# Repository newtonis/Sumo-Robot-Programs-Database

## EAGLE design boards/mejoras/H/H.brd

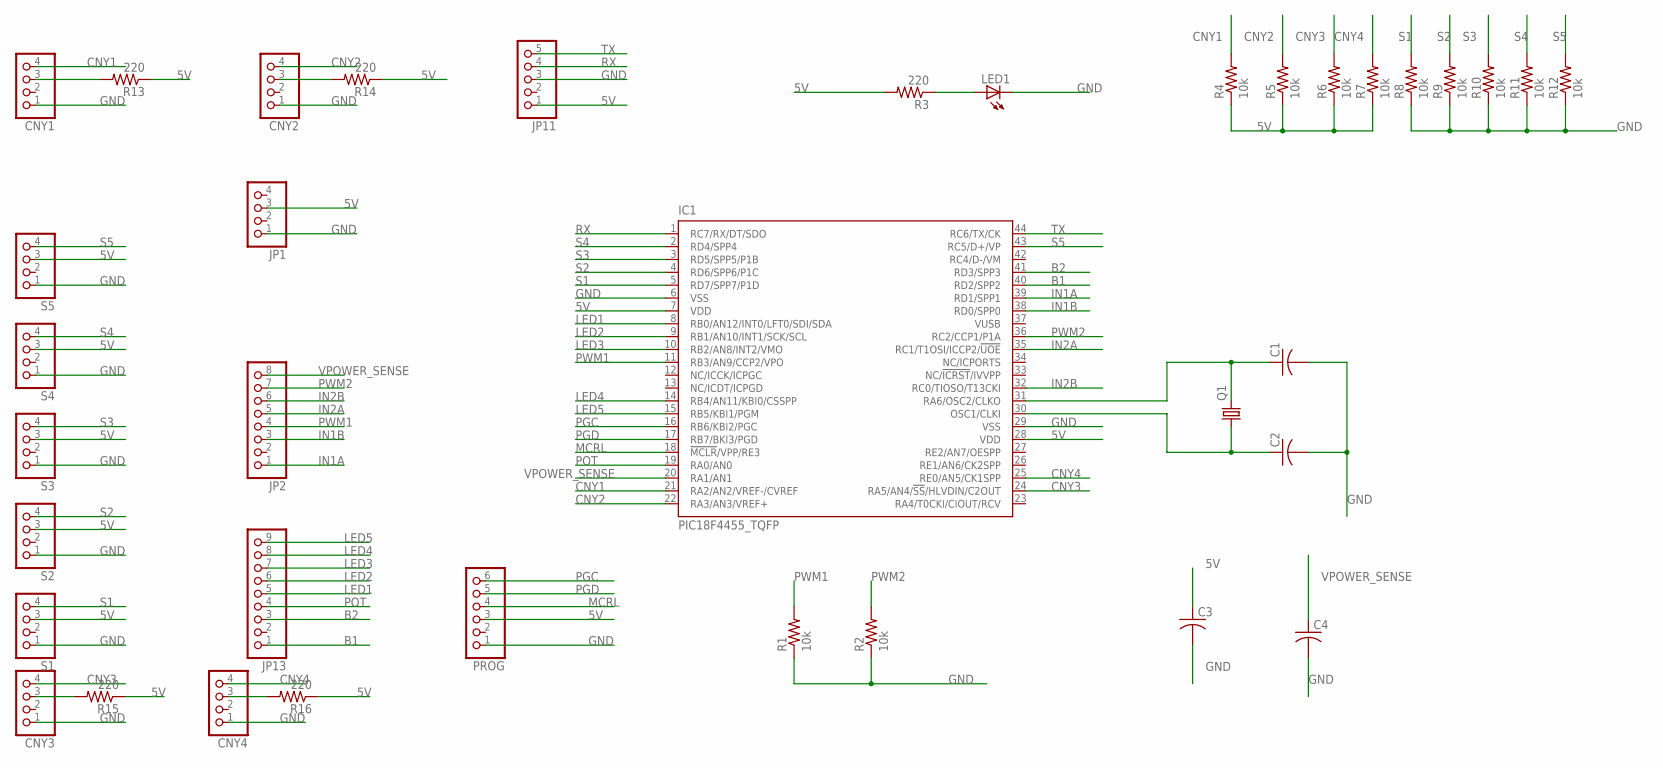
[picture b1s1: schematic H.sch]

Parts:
C1, C2, C3, C4: C-USC0805K; C0805K
CNY1, CNY2, CNY3, CNY4: PINHD-1X4/90; 1X04/90
IC1: PIC18F4455_TQFP; TQFP44
JP1: PINHD-1X4/90; 1X04/90
JP2: PINHD-1X8/90; 1X08/90
JP11: PINHD-1X5/90; 1X05/90
JP13: PINHD-1X9/90; 1X09/90
LED1: LEDCHIPLED_1206; CHIPLED_1206
PROG: PINHD-1X6/90; 1X06/90
Q1: CRYSTALHC49S; HC49/S
R1, R2, R4, R5, R6, R7, R8, R9, R10, R11, R12: 10k; M1206
R3, R13, R14, R15, R16: 220; M1206
S1, S2, S3, S4, S5: PINHD-1X4/90; 1X04/90

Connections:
5V: C3.1, IC1.7 (VDD), IC1.28 (VDD), JP1.3, JP11.1, PROG.3, R3.2, R4.1, R5.1, R6.1, R7.1, R13.1, R14.1, R15.1, R16.1, S1.3, S2.3, S3.3, S4.3, S5.3
B1: IC1.40 (RD2/SPP2), JP13.1
B2: IC1.41 (RD3/SPP3), JP13.3
CNY1: CNY1.4, IC1.21 (RA2/AN2/VREF-/CVREF), R4.2
CNY2: CNY2.4, IC1.22 (RA3/AN3/VREF+), R5.2
CNY3: CNY3.4, IC1.24 (RA5/AN4/!SS!/HLVDIN/C2OUT), R6.2
CNY4: CNY4.4, IC1.25 (RE0/AN5/CK1SPP), R7.2
GND: C1.2, C2.2, C3.2, C4.2, CNY1.1, CNY2.1, CNY3.1, CNY4.1, IC1.6 (VSS), IC1.29 (VSS), JP1.1, JP11.3, LED1.C, PROG.1, R1.1, R2.1, R8.1, R9.1, R10.1, R11.1, R12.1, S1.1, S2.1, S3.1, S4.1, S5.1
IN1A: IC1.39 (RD1/SPP1), JP2.1
IN1B: IC1.38 (RD0/SPP0), JP2.3
IN2A: IC1.35 (RC1/T1OSI/ICCP2/!UOE), JP2.5
IN2B: IC1.32 (RC0/TIOSO/T13CKI), JP2.6
LED1: IC1.8 (RB0/AN12/INT0/LFT0/SDI/SDA), JP13.5
LED2: IC1.9 (RB1/AN10/INT1/SCK/SCL), JP13.6
LED3: IC1.10 (RB2/AN8/INT2/VMO), JP13.7
LED4: IC1.14 (RB4/AN11/KBI0/CSSPP), JP13.8
LED5: IC1.15 (RB5/KBI1/PGM), JP13.9
MCRL: IC1.18 (!MCLR!/VPP/RE3), PROG.4
unnamed: C1.1, IC1.31 (RA6/OSC2/CLKO), Q1.2
unnamed: C2.1, IC1.30 (OSC1/CLKI), Q1.1
unnamed: LED1.A, R3.1
unnamed: CNY1.3, R13.2
unnamed: CNY2.3, R14.2
unnamed: CNY3.3, R15.2
unnamed: CNY4.3, R16.2
PGC: IC1.16 (RB6/KBI2/PGC), PROG.6
PGD: IC1.17 (RB7/BKI3/PGD), PROG.5
POT: IC1.19 (RA0/AN0), JP13.4
PWM1: IC1.11 (RB3/AN9/CCP2/VPO), JP2.4, R1.2
PWM2: IC1.36 (RC2/CCP1/P1A), JP2.7, R2.2
RX: IC1.1 (RC7/RX/DT/SDO), JP11.4
S1: IC1.5 (RD7/SPP7/P1D), R8.2, S1.4
S2: IC1.4 (RD6/SPP6/P1C), R9.2, S2.4
S3: IC1.3 (RD5/SPP5/P1B), R10.2, S3.4
S4: IC1.2 (RD4/SPP4), R11.2, S4.4
S5: IC1.43 (RC5/D+/VP), R12.2, S5.4
TX: IC1.44 (RC6/TX/CK), JP11.5
VPOWER_SENSE: C4.1, IC1.20 (RA1/AN1), JP2.8

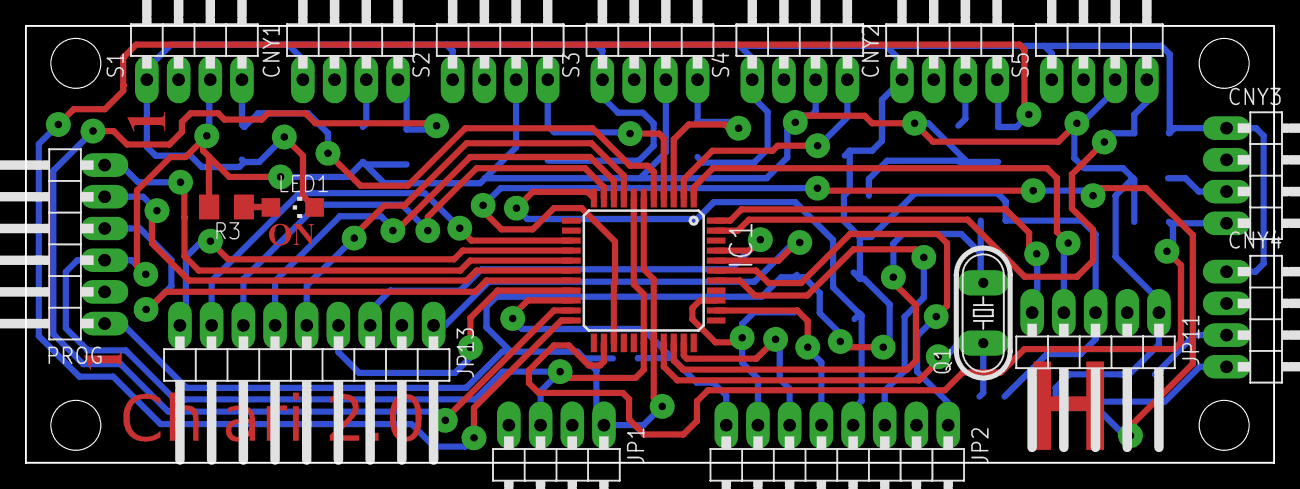
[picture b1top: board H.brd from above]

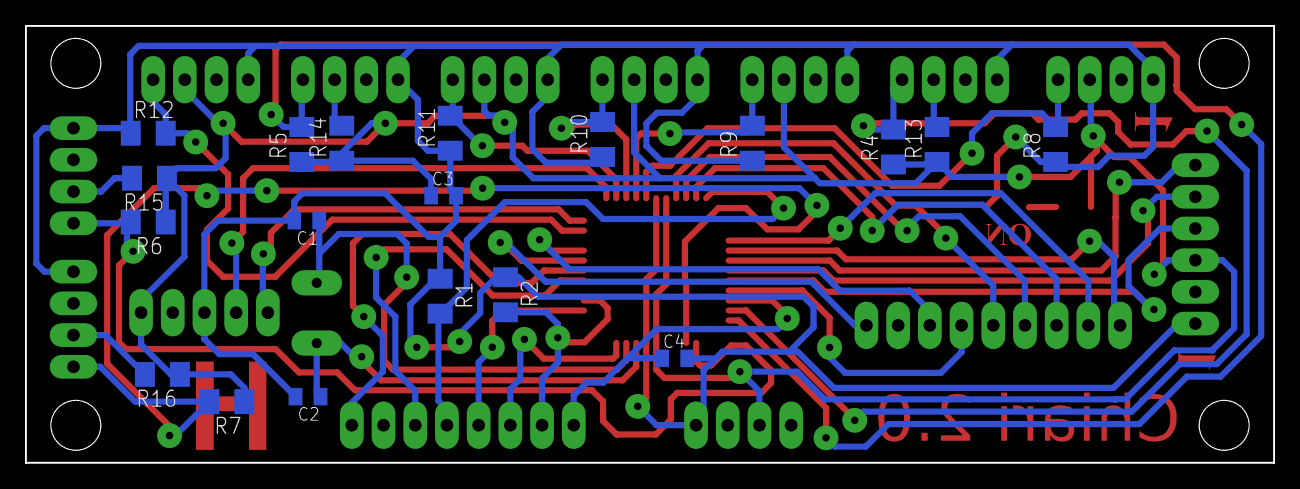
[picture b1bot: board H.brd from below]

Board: 2 copper layers, 100.0 x 35.0 mm, 37 parts (19 on the bottom side), 38 nets.

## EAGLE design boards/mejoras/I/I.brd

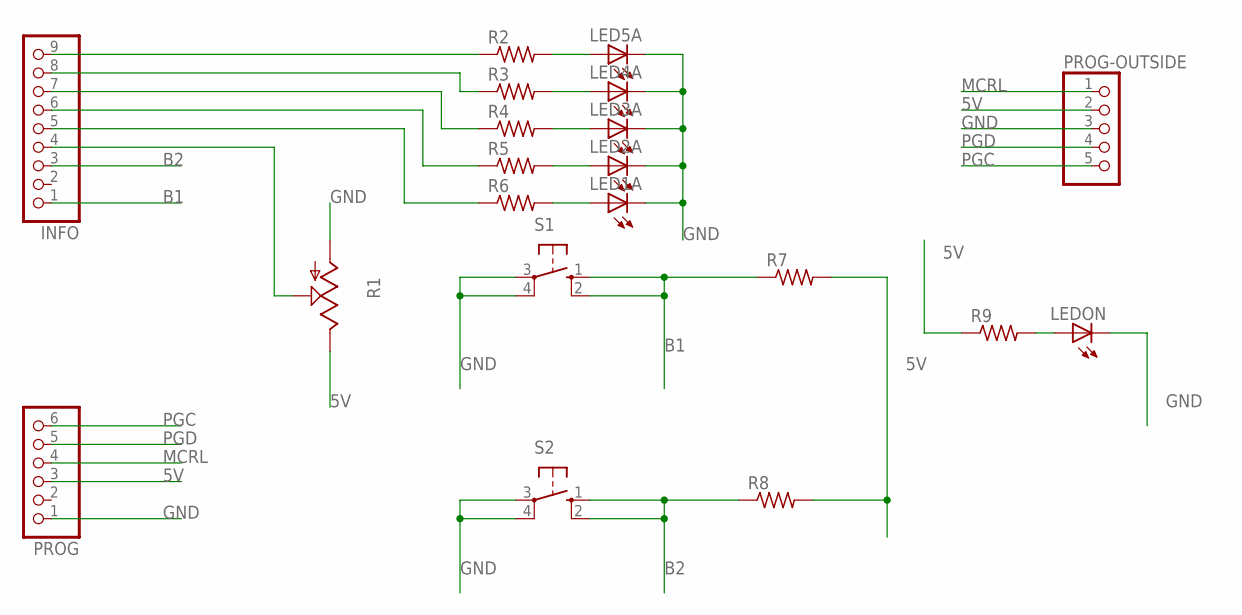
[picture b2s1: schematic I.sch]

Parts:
INFO: PINHD-1X9/90; 1X09/90
LED1A, LED2A, LED3A, LED4A, LED5A: LEDCHIPLED_1206; CHIPLED_1206
LEDON: LEDCHIPLED_1206; CHIPLED_1206
PROG: PINHD-1X6/90; 1X06/90
PROG-OUTSIDE: PINHD-1X5/90; 1X05/90
R1: TRIM_US-CA6V; CA6V
R2, R3, R4, R5, R6, R7, R8, R9: R-US_M1206; M1206
S1, S2: 10-XX; B3F-10XX

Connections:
5V: PROG.3, PROG-OUTSIDE.2, R1.E, R7.2, R8.2, R9.1
B1: INFO.1, R7.1, S1.1 (S), S1.2 (S1)
B2: INFO.3, R8.1, S2.1 (S), S2.2 (S1)
GND: LED1A.C, LED2A.C, LED3A.C, LED4A.C, LED5A.C, LEDON.C, PROG.1, PROG-OUTSIDE.3, R1.A, S1.3, S1.4 (P1), S2.3, S2.4 (P1)
MCRL: PROG.4, PROG-OUTSIDE.1
unnamed: LED1A.A, R6.2
unnamed: LED2A.A, R5.2
unnamed: LED3A.A, R4.2
unnamed: LED4A.A, R3.2
unnamed: LED5A.A, R2.2
unnamed: INFO.9, R2.1
unnamed: INFO.8, R3.1
unnamed: INFO.7, R4.1
unnamed: INFO.6, R5.1
unnamed: INFO.5, R6.1
unnamed: INFO.4, R1.S
unnamed: LEDON.A, R9.2
PGC: PROG.6, PROG-OUTSIDE.5
PGD: PROG.5, PROG-OUTSIDE.4

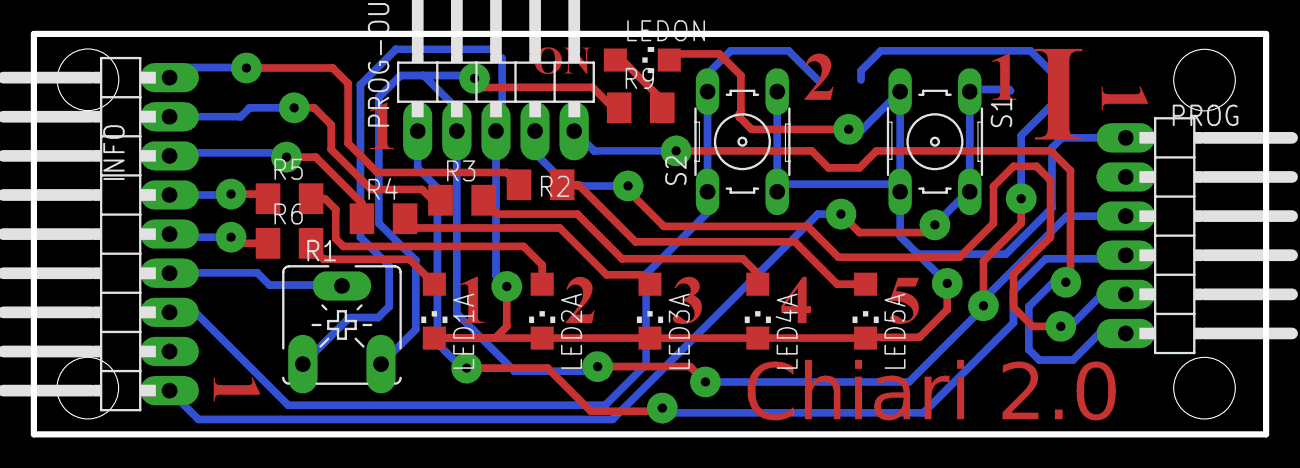
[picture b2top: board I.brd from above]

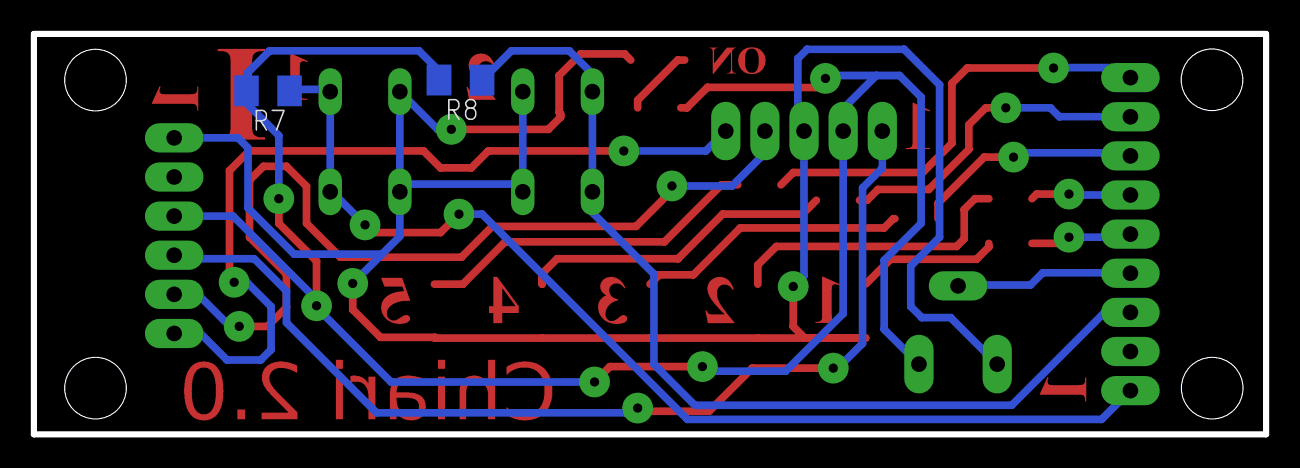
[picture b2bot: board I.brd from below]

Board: 2 copper layers, 80.0 x 26.0 mm, 20 parts (2 on the bottom side), 19 nets.

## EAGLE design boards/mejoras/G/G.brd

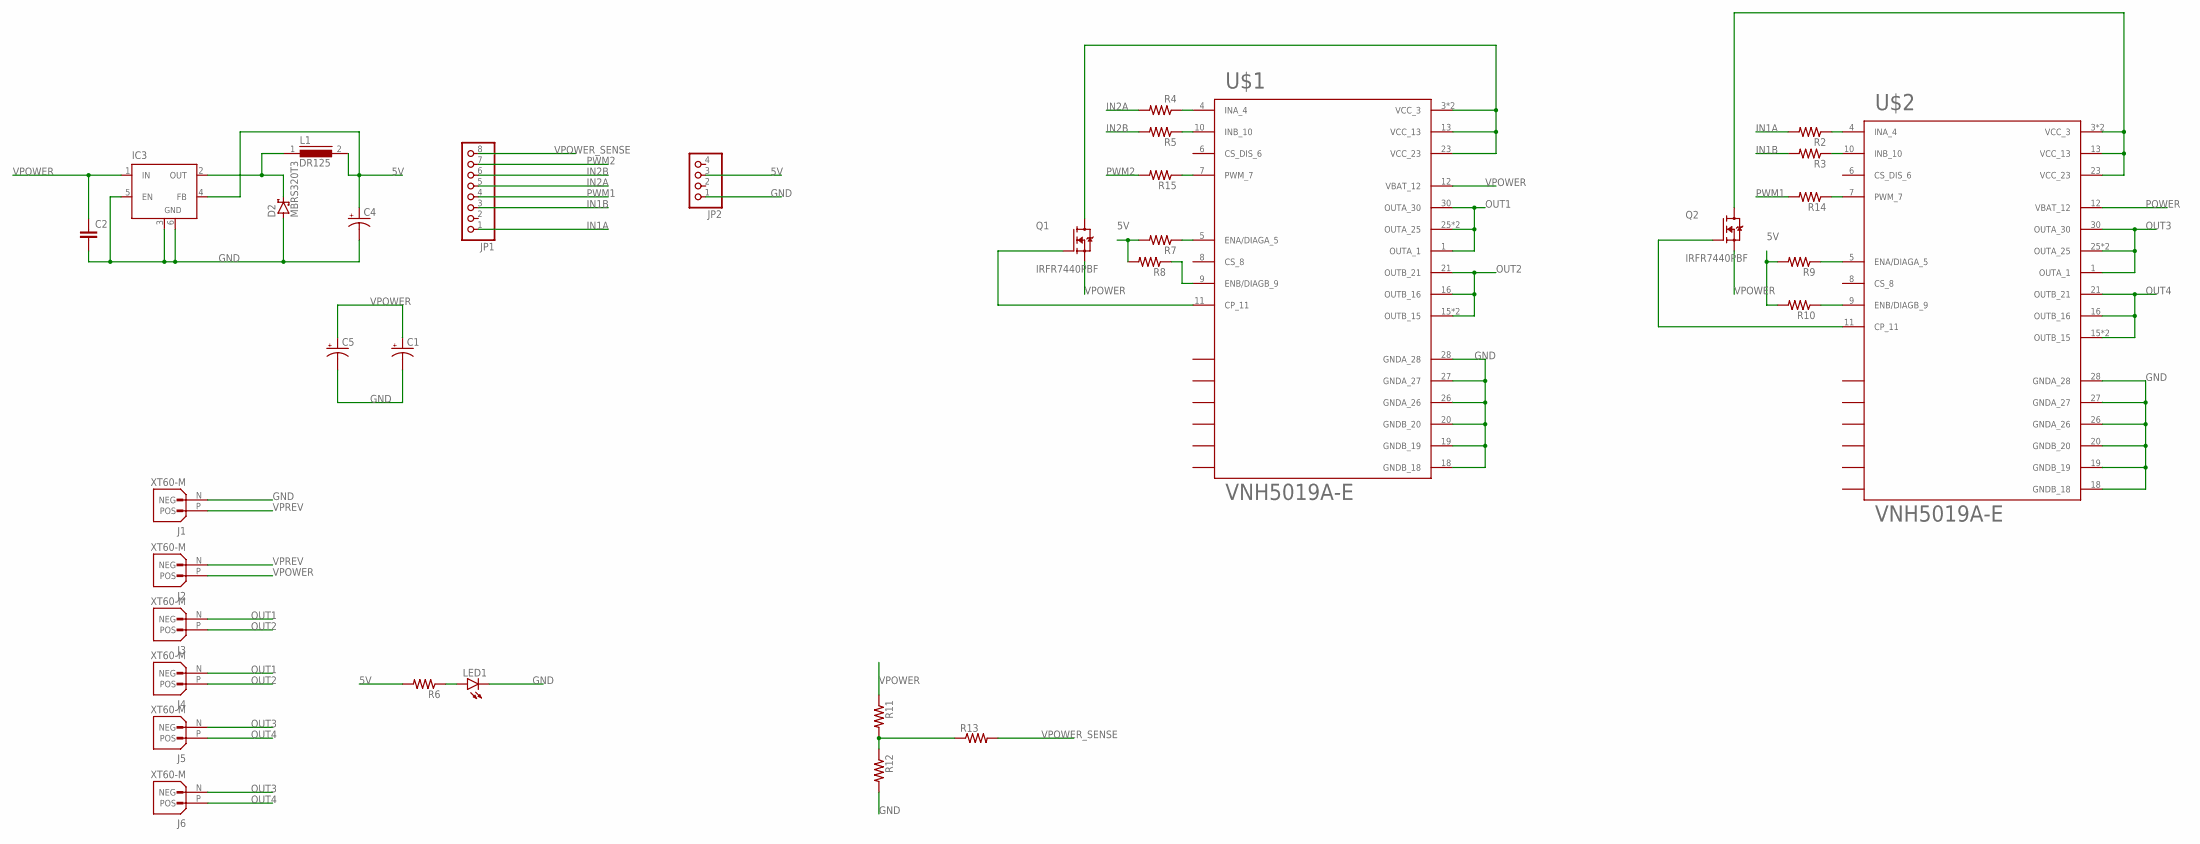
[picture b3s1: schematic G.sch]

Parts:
C1, C5: CPOL-US153CLV-1014; 153CLV-1014
C2: C2.5/5; C2.5-5
C4: CAP_POLH13; PANASONIC_H13
D2: MBRS320T3; SMC
IC3: LM2596S; TO263-5
J1, J2, J3, J4, J5, J6: XT60-M; AMASS_XT60-M
JP1: PINHD-1X8/90; 1X08/90
JP2: PINHD-1X4/90; 1X04/90
L1: DR125
LED1: LEDSML1206; SML1206
Q1, Q2: IRFR7440PBF; TO229P990X239-3N
R2, R3, R4, R5, R6, R7, R8, R9, R10, R11, R12, R13, R14, R15: R-US_M1206; M1206
U$1, U$2: VNH5019A-E; IC_MULTIPOWERSO-30TR

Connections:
5V: C4.+, IC3.4 (FB), JP2.3, L1.2, R6.2, R7.2, R8.2, R9.2, R10.2
GND: C1.-, C2.2, C4.-, C5.-, D2.A, IC3.3 (GND), IC3.5 (EN), IC3.6 (GND), J1.N (NEG), JP2.1, LED1.C, R12.2, U$1.18 (GNDB_18), U$1.19 (GNDB_19), U$1.20 (GNDB_20), U$1.26 (GNDA_26), U$1.27 (GNDA_27), U$1.28 (GNDA_28), U$2.19 (GNDB_19), U$2.20 (GNDB_20), U$2.26 (GNDA_26), U$2.27 (GNDA_27), U$2.28 (GNDA_28); also elsewhere on the board
IN1A: JP1.1, R2.2
IN1B: JP1.3, R3.2
IN2A: JP1.5, R4.2
IN2B: JP1.6, R5.2
unnamed: Q1.1 (G), U$1.11 (CP_11)
unnamed: R7.1, U$1.5 (ENA/DIAGA_5)
unnamed: LED1.A, R6.1
unnamed: R8.1, U$1.9 (ENB/DIAGB_9)
unnamed: R9.1, U$2.5 (ENA/DIAGA_5)
unnamed: R10.1, U$2.9 (ENB/DIAGB_9)
unnamed: R11.2, R12.1, R13.1
unnamed: R4.1, U$1.4 (INA_4)
unnamed: R5.1, U$1.10 (INB_10)
unnamed: R2.1, U$2.4 (INA_4)
unnamed: R3.1, U$2.10 (INB_10)
unnamed: D2.C, IC3.2 (OUT), L1.1
unnamed: R15.1, U$1.7 (PWM_7)
unnamed: R14.1, U$2.7 (PWM_7)
unnamed: Q1.4 (D), U$1.3 (VCC_3), U$1.13 (VCC_13), U$1.23 (VCC_23), U$1.HS1 (VCC_3)
unnamed: Q2.1 (G), U$2.11 (CP_11)
unnamed: Q2.4 (D), U$2.3 (VCC_3), U$2.13 (VCC_13), U$2.23 (VCC_23), U$2.HS1 (VCC_3)
unnamed 23: U$1.8 (CS_8); also elsewhere on the board
unnamed 24: U$2.8 (CS_8); also elsewhere on the board
OUT1: J3.N (NEG), J4.N (NEG), U$1.1 (OUTA_1), U$1.25 (OUTA_25), U$1.30 (OUTA_30), U$1.HS2 (OUTA_25)
OUT2: J3.P (POS), J4.P (POS), U$1.15 (OUTB_15), U$1.16 (OUTB_16), U$1.21 (OUTB_21), U$1.HS3 (OUTB_15)
OUT3: J5.N (NEG), J6.N (NEG), U$2.1 (OUTA_1), U$2.25 (OUTA_25), U$2.30 (OUTA_30), U$2.HS2 (OUTA_25)
OUT4: J5.P (POS), J6.P (POS), U$2.15 (OUTB_15), U$2.16 (OUTB_16), U$2.21 (OUTB_21), U$2.HS3 (OUTB_15)
PWM1: JP1.4, R14.2
PWM2: JP1.7, R15.2
VPOWER_SENSE: JP1.8, R13.2
VPREV: J1.P (POS), J2.N (NEG)

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
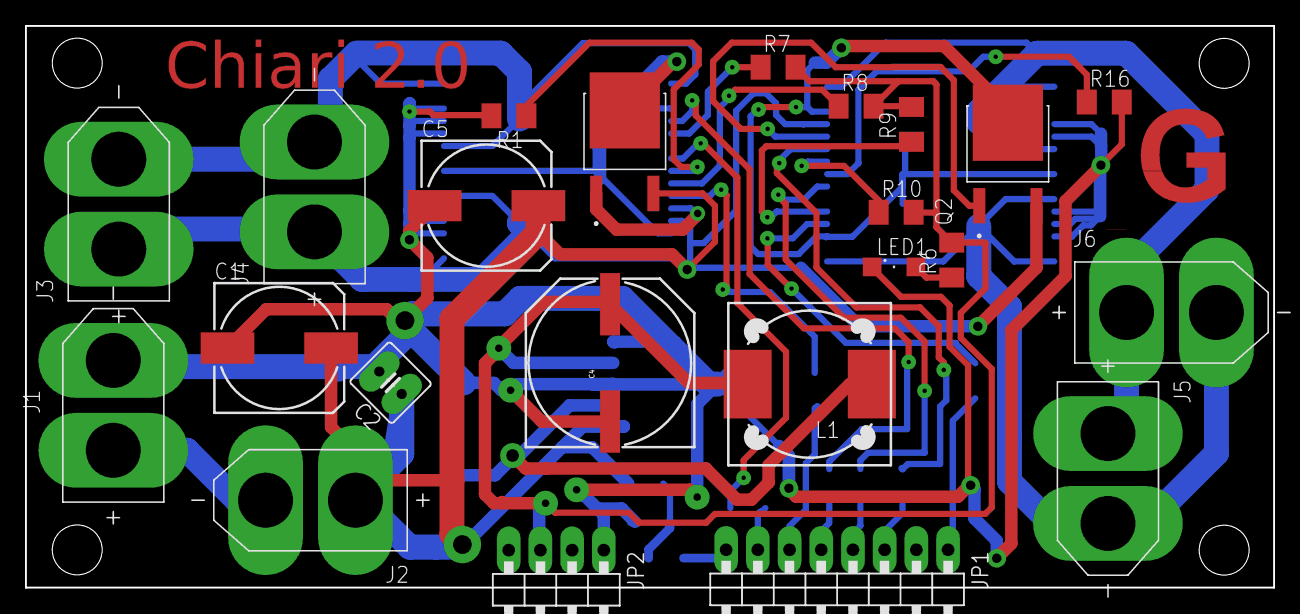
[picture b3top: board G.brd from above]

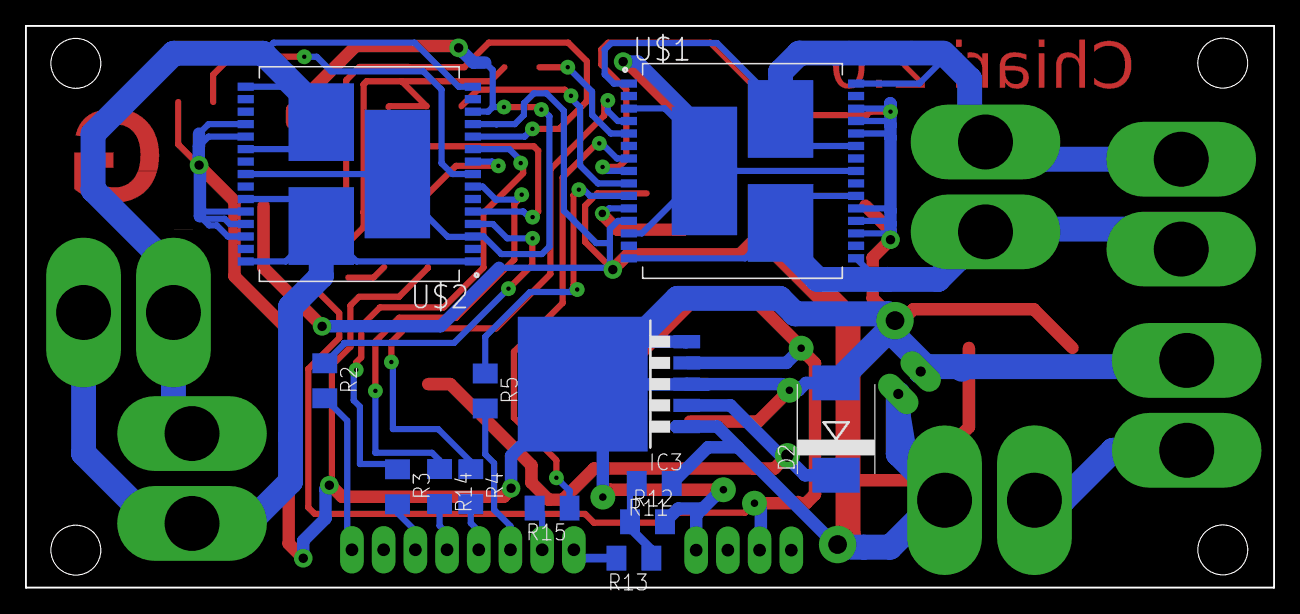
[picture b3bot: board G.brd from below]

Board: 2 copper layers, 100.0 x 45.0 mm, 36 parts (13 on the bottom side), 34 nets.

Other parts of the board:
R1, R16: M1206

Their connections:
GND: R1.2, R16.2; also elsewhere on the board
unnamed 23: R1.1; also elsewhere on the board
unnamed 24: R16.1; also elsewhere on the board

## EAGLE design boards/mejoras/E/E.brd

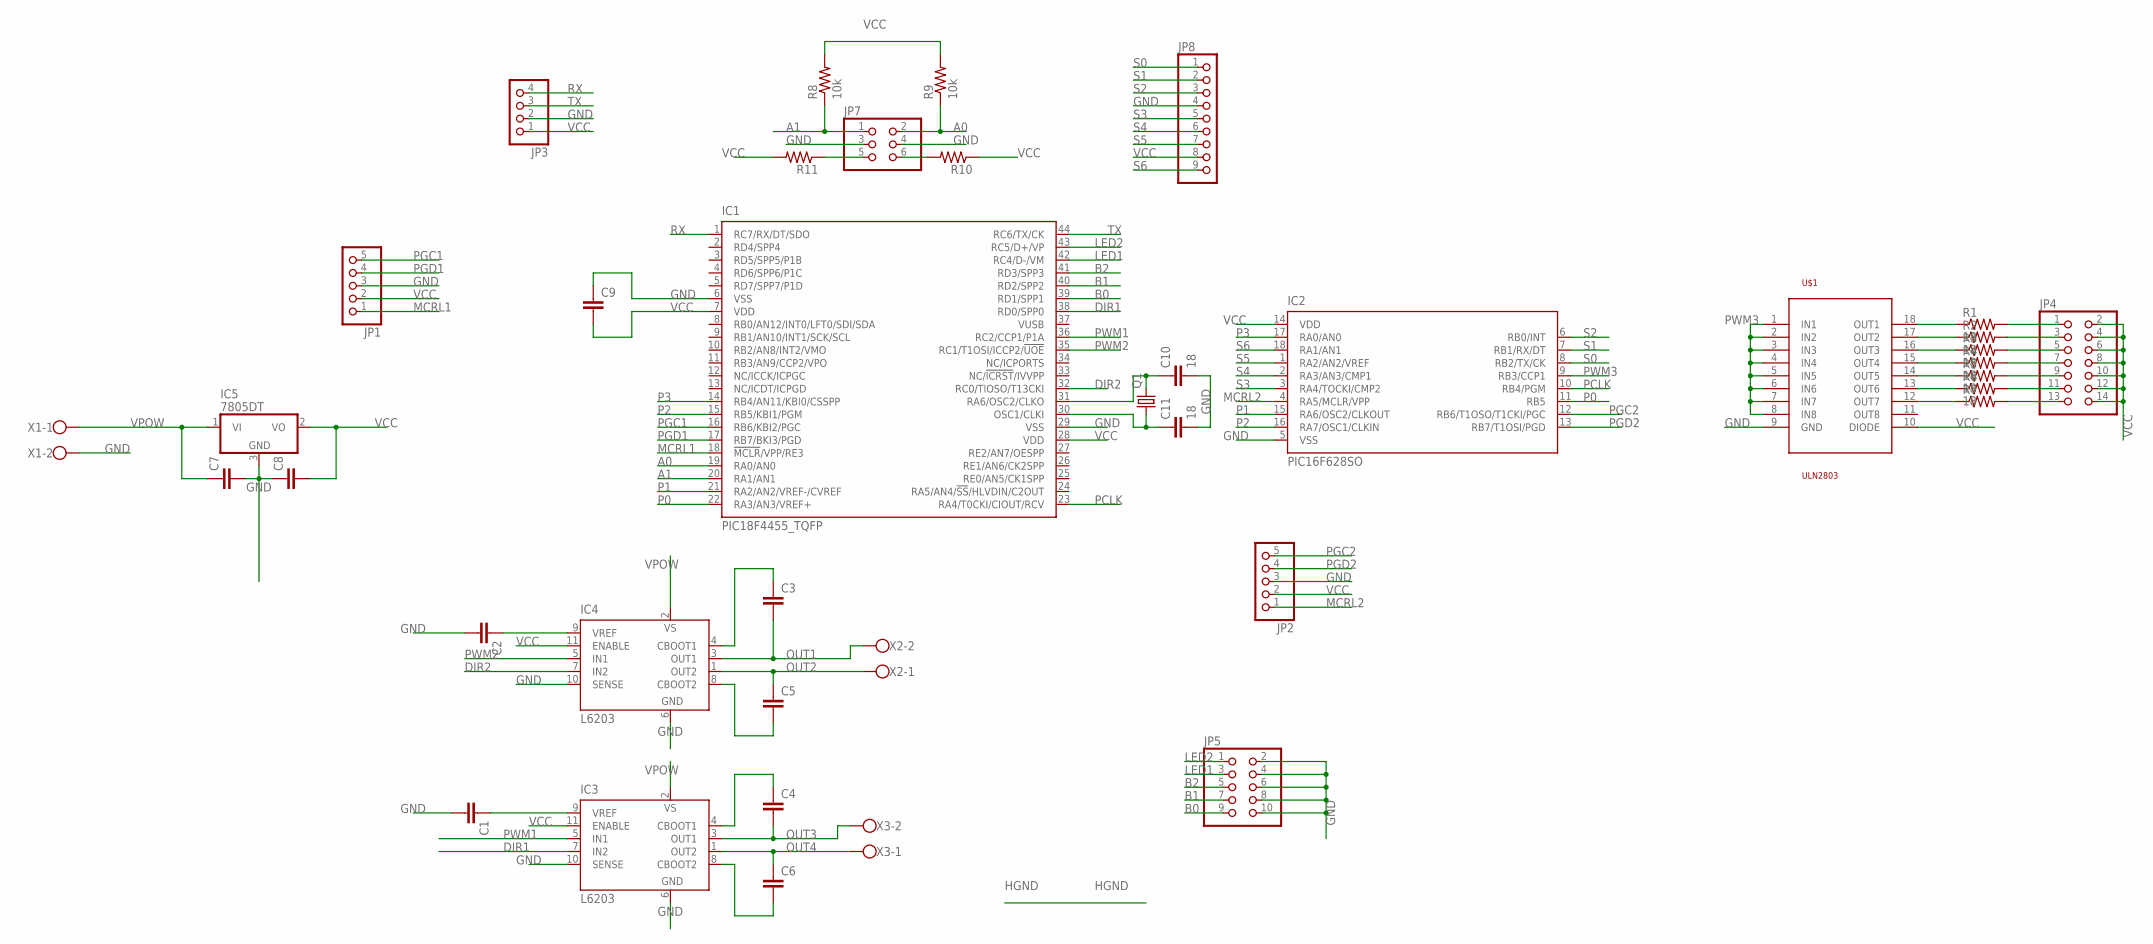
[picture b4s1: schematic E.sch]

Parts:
C1, C2, C3, C4, C5, C6, C7, C8, C9: C2,5-3; C2.5-3
C10, C11: 18; C2.5-3
IC1: PIC18F4455_TQFP; TQFP44
IC2: PIC16F628SO; SO-18W
IC3, IC4: L6203; MULTIWATT-11
IC5: 7805DT; TO252
JP1, JP2: PINHD-1X5; 1X05
JP3: PINHD-1X4; 1X04
JP4: PINHD-2X7; 2X07
JP5: PINHD-2X5; 2X05
JP7: PINHD-2X3; 2X03
JP8: PINHD-1X9; 1X09
Q1: CRYSTALHC49S; HC49/S
R1, R2, R3, R4, R5, R6: 18; M1206
R7, R10, R11: R-US_M1206; M1206
R8, R9: 10k; M1206
U$1: ULN2803; SO18L
X1, X2, X3: W237-102

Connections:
A0: IC1.19 (RA0/AN0), JP7.2, R9.1
A1: IC1.20 (RA1/AN1), JP7.1, R8.1
B0: IC1.39 (RD1/SPP1), JP5.9
B1: IC1.40 (RD2/SPP2), JP5.7
B2: IC1.41 (RD3/SPP3), JP5.5
DIR1: IC1.38 (RD0/SPP0), IC3.7 (IN2)
DIR2: IC1.32 (RC0/TIOSO/T13CKI), IC4.7 (IN2)
GND: C1.2, C2.2, C7.2, C8.1, C9.1, C10.2, C11.2, IC1.6 (VSS), IC1.29 (VSS), IC2.5 (VSS), IC3.6 (GND), IC3.10 (SENSE), IC4.6 (GND), IC4.10 (SENSE), IC5.3 (GND), JP1.3, JP2.3, JP3.2, JP5.2, JP5.4, JP5.6, JP5.8, JP5.10, JP7.3, JP7.4, JP8.4, U$1.9 (GND), X1.2
LED1: IC1.42 (RC4/D-/VM), JP5.3
LED2: IC1.43 (RC5/D+/VP), JP5.1
MCRL1: IC1.18 (!MCLR!/VPP/RE3), JP1.1
MCRL2: IC2.4 (RA5/MCLR/VPP), JP2.1
unnamed: C1.1, IC3.9 (VREF)
unnamed: C2.1, IC4.9 (VREF)
unnamed: C3.1, IC4.4 (CBOOT1)
unnamed: C4.1, IC3.4 (CBOOT1)
unnamed: C5.2, IC4.8 (CBOOT2)
unnamed: C6.2, IC3.8 (CBOOT2)
unnamed: R1.1, U$1.18 (OUT1)
unnamed: R2.1, U$1.17 (OUT2)
unnamed: R3.1, U$1.16 (OUT3)
unnamed: R4.1, U$1.15 (OUT4)
unnamed: R5.1, U$1.14 (OUT5)
unnamed: R6.1, U$1.13 (OUT6)
unnamed: R7.1, U$1.12 (OUT7)
unnamed: JP4.13, R7.2
unnamed: JP4.11, R6.2
unnamed: JP4.9, R5.2
unnamed: JP4.7, R4.2
unnamed: JP4.5, R3.2
unnamed: JP4.3, R2.2
unnamed: JP4.1, R1.2
unnamed: JP7.5, R11.1
unnamed: JP7.6, R10.2
unnamed: C11.1, IC1.30 (OSC1/CLKI), Q1.1
unnamed: C10.1, IC1.31 (RA6/OSC2/CLKO), Q1.2
OUT1: C3.2, IC4.3 (OUT1), X2.2
OUT2: C5.1, IC4.1 (OUT2), X2.1
OUT3: C4.2, IC3.3 (OUT1), X3.2
OUT4: C6.1, IC3.1 (OUT2), X3.1
P0: IC1.22 (RA3/AN3/VREF+), IC2.11 (RB5)
P1: IC1.21 (RA2/AN2/VREF-/CVREF), IC2.15 (RA6/OSC2/CLKOUT)
P2: IC1.15 (RB5/KBI1/PGM), IC2.16 (RA7/OSC1/CLKIN)
P3: IC1.14 (RB4/AN11/KBI0/CSSPP), IC2.17 (RA0/AN0)
PCLK: IC1.23 (RA4/T0CKI/CIOUT/RCV), IC2.10 (RB4/PGM)
PGC1: IC1.16 (RB6/KBI2/PGC), JP1.5
PGC2: IC2.12 (RB6/T1OSO/T1CKI/PGC), JP2.5
PGD1: IC1.17 (RB7/BKI3/PGD), JP1.4
PGD2: IC2.13 (RB7/T1OSI/PGD), JP2.4
PWM1: IC1.36 (RC2/CCP1/P1A), IC3.5 (IN1)
PWM2: IC1.35 (RC1/T1OSI/ICCP2/!UOE), IC4.5 (IN1)
PWM3: IC2.9 (RB3/CCP1), U$1.1 (IN1), U$1.2 (IN2), U$1.3 (IN3), U$1.4 (IN4), U$1.5 (IN5), U$1.6 (IN6), U$1.7 (IN7), U$1.8 (IN8)
RX: IC1.1 (RC7/RX/DT/SDO), JP3.4
S0: IC2.8 (RB2/TX/CK), JP8.1
S1: IC2.7 (RB1/RX/DT), JP8.2
S2: IC2.6 (RB0/INT), JP8.3
S3: IC2.3 (RA4/TOCKI/CMP2), JP8.5
S4: IC2.2 (RA3/AN3/CMP1), JP8.6
S5: IC2.1 (RA2/AN2/VREF), JP8.7
S6: IC2.18 (RA1/AN1), JP8.9
TX: IC1.44 (RC6/TX/CK), JP3.3
VCC: C8.2, C9.2, IC1.7 (VDD), IC1.28 (VDD), IC2.14 (VDD), IC3.11 (ENABLE), IC4.11 (ENABLE), IC5.2 (VO), JP1.2, JP2.2, JP3.1, JP4.2, JP4.4, JP4.6, JP4.8, JP4.10, JP4.12, JP4.14, JP8.8, R8.2, R9.2, R10.1, R11.2, U$1.10 (DIODE)
VPOW: C7.1, IC3.2 (VS), IC4.2 (VS), IC5.1 (VI), X1.1

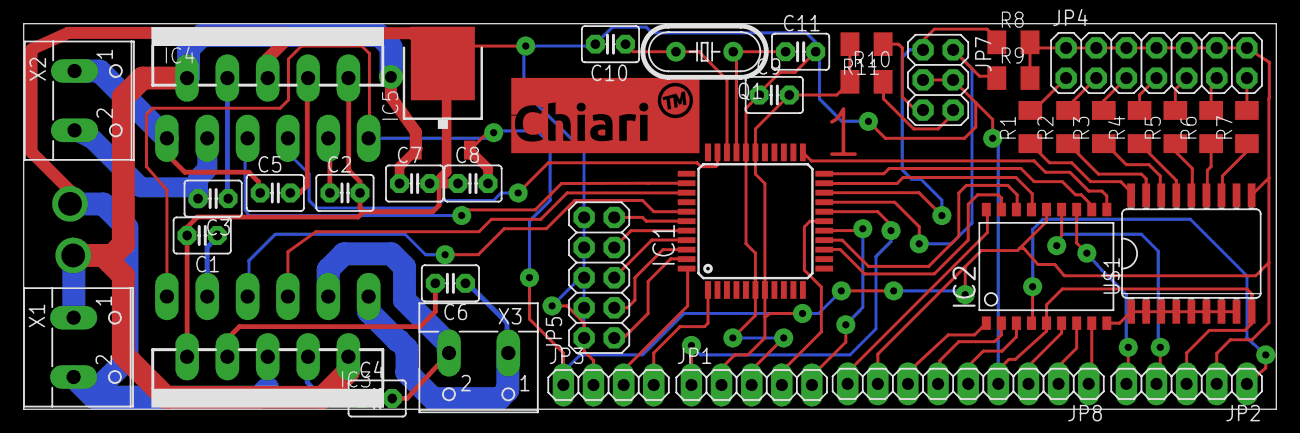
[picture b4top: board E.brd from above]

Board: 2 copper layers, 105.6 x 32.5 mm, 39 parts (0 on the bottom side), 63 nets.

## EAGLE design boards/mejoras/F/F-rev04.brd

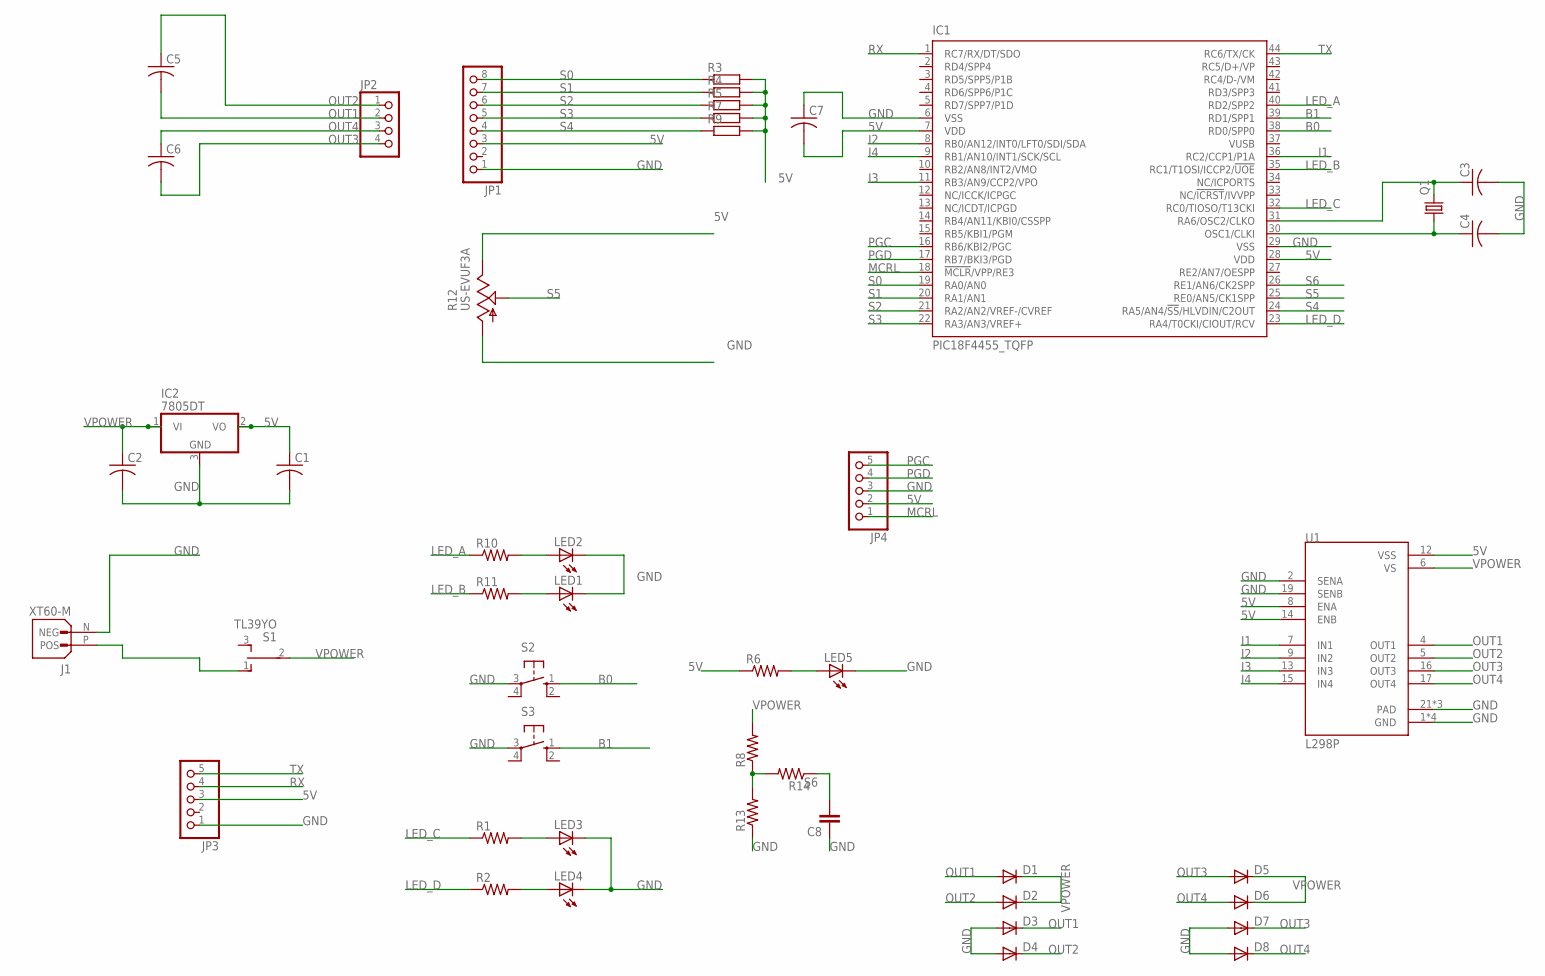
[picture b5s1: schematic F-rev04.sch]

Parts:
C1, C2, C3, C4, C5, C6, C7: C-USC0805K; C0805K
C8: C2,5-3; C2.5-3
D1, D2, D3, D4, D5, D6, D7, D8: DIODE-DO214AC; DO214AC
IC1: PIC18F4455_TQFP; TQFP44
IC2: 7805DT; TO252
J1: XT60-M; AMASS_XT60-M
JP1: PINHD-1X8; 1X08
JP2: PINHD-1X4; 1X04
JP3, JP4: PINHD-1X5; 1X05
LED1, LED2, LED3, LED4, LED5: LEDCHIPLED_1206; CHIPLED_1206
Q1: CRYSTALHC49S; HC49/S
R1, R2: R-US_R0805; R0805
R3, R4, R5, R7, R9: R-EU_M0805; M0805
R6, R8, R10, R11, R13, R14: R-US_M0805; M0805
R12: US-EVUF3A; EVUF
S1: TL39YO; TL3XYO
S2, S3: 10-XX; B3F-10XX
U1: L298P; SOIC127P1420X360-20N

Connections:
5V: C1.1, C7.2, IC1.7 (VDD), IC1.28 (VDD), IC2.2 (VO), JP1.3, JP3.3, JP4.2, R3.2, R4.2, R5.2, R6.1, R7.2, R9.2, R12.3 (E), U1.8 (ENA), U1.12 (VSS), U1.14 (ENB)
B0: IC1.38 (RD0/SPP0), S2.1 (S)
B1: IC1.39 (RD1/SPP1), S3.1 (S)
GND: C1.2, C2.2, C3.2, C4.2, C7.1, C8.1, D3.A, D4.A, D7.A, D8.A, IC1.6 (VSS), IC1.29 (VSS), IC2.3 (GND), J1.N (NEG), JP1.1, JP3.1, JP4.3, LED1.C, LED2.C, LED3.C, LED4.C, LED5.C, R12.1 (A), R13.1, S2.3, S3.3, U1.1 (GND), U1.2 (SENA), U1.10 (GND), U1.11 (GND), U1.19 (SENB), U1.20 (GND), U1.21 (PAD), U1.22 (PAD), U1.23 (PAD)
I1: IC1.36 (RC2/CCP1/P1A), U1.7 (IN1)
I2: IC1.8 (RB0/AN12/INT0/LFT0/SDI/SDA), U1.9 (IN2)
I3: IC1.11 (RB3/AN9/CCP2/VPO), U1.13 (IN3)
I4: IC1.9 (RB1/AN10/INT1/SCK/SCL), U1.15 (IN4)
LED_A: IC1.40 (RD2/SPP2), R10.1
LED_B: IC1.35 (RC1/T1OSI/ICCP2/!UOE), R11.1
LED_C: IC1.32 (RC0/TIOSO/T13CKI), R1.1
LED_D: IC1.23 (RA4/T0CKI/CIOUT/RCV), R2.1
MCRL: IC1.18 (!MCLR!/VPP/RE3), JP4.1
unnamed: C4.1, IC1.30 (OSC1/CLKI), Q1.1
unnamed: C3.1, IC1.31 (RA6/OSC2/CLKO), Q1.2
unnamed: R8.1, R13.2, R14.2
unnamed: LED2.A, R10.2
unnamed: LED1.A, R11.2
unnamed: LED3.A, R1.2
unnamed: LED4.A, R2.2
unnamed: LED5.A, R6.2
OUT1: C5.2, D1.A, D3.C, JP2.2, U1.4 (OUT1)
OUT2: C5.1, D2.A, D4.C, JP2.1, U1.5 (OUT2)
OUT3: C6.2, D5.A, D7.C, JP2.4, U1.16 (OUT3)
OUT4: C6.1, D6.A, D8.C, JP2.3, U1.17 (OUT4)
PGC: IC1.16 (RB6/KBI2/PGC), JP4.5
PGD: IC1.17 (RB7/BKI3/PGD), JP4.4
RX: IC1.1 (RC7/RX/DT/SDO), JP3.4
S0: IC1.19 (RA0/AN0), JP1.8, R3.1
S1: IC1.20 (RA1/AN1), JP1.7, R4.1
S2: IC1.21 (RA2/AN2/VREF-/CVREF), JP1.6, R5.1
S3: IC1.22 (RA3/AN3/VREF+), JP1.5, R7.1
S4: IC1.24 (RA5/AN4/!SS!/HLVDIN/C2OUT), JP1.4, R9.1
S5: IC1.25 (RE0/AN5/CK1SPP), R12.2 (S)
S6: C8.2, IC1.26 (RE1/AN6/CK2SPP), R14.1
TX: IC1.44 (RC6/TX/CK), JP3.5
VPOWER: C2.1, D1.C, D2.C, D5.C, D6.C, IC2.1 (VI), R8.2, S1.2, U1.6 (VS)
VPREV: J1.P (POS), S1.1 (O)

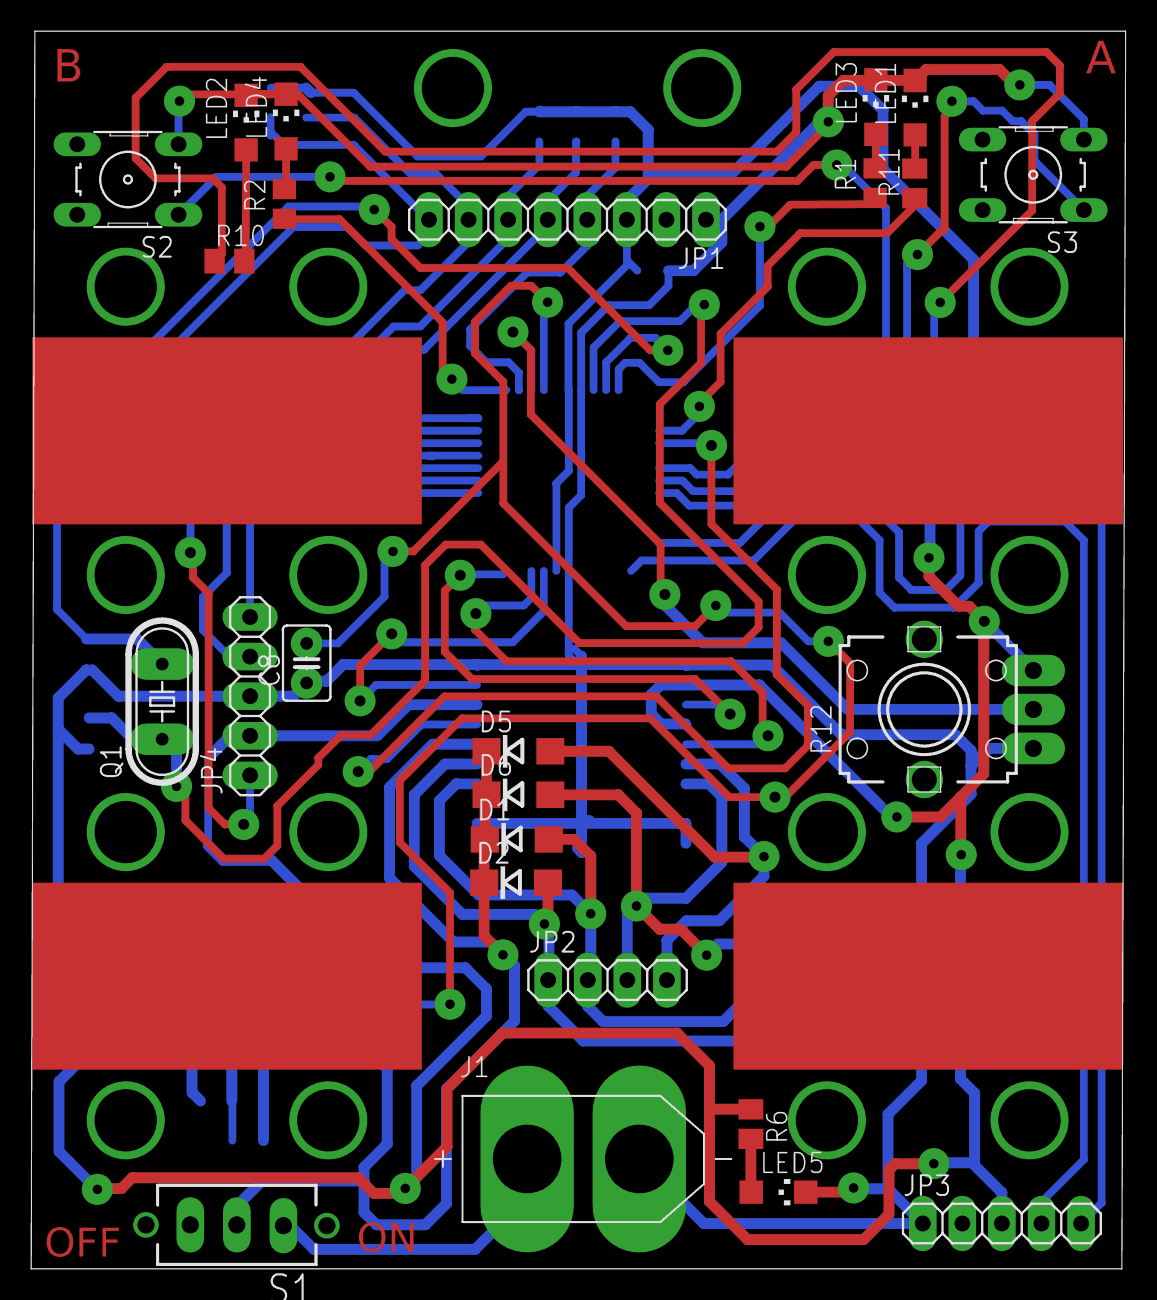
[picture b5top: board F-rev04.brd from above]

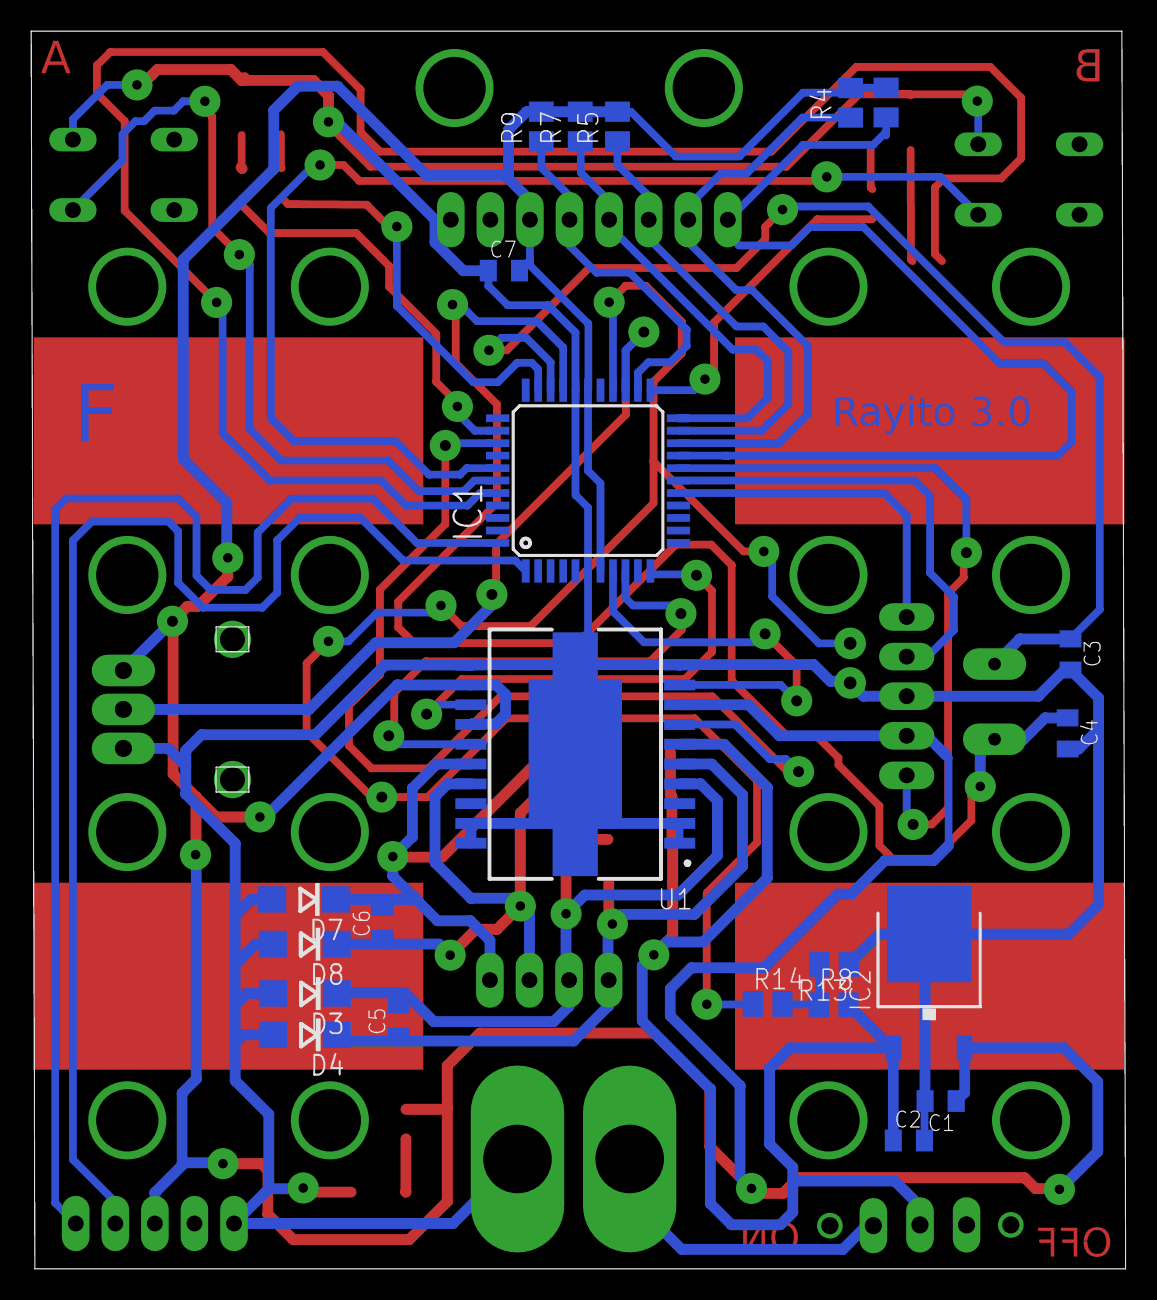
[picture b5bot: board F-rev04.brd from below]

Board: 2 copper layers, 70.2 x 79.4 mm, 47 parts (22 on the bottom side), 38 nets.

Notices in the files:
parts and their libraries:
SparkFun: Licensing: CC v3.0 Share-Alike You are welcome to use this library for commercial purposes.
